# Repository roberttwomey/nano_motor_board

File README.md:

# nano-motor-board
a motor driver adapter for use with 3-axis GRBL.
connects arduino nano to pololu driver boards.

rtwomey@ysu.edu
2017

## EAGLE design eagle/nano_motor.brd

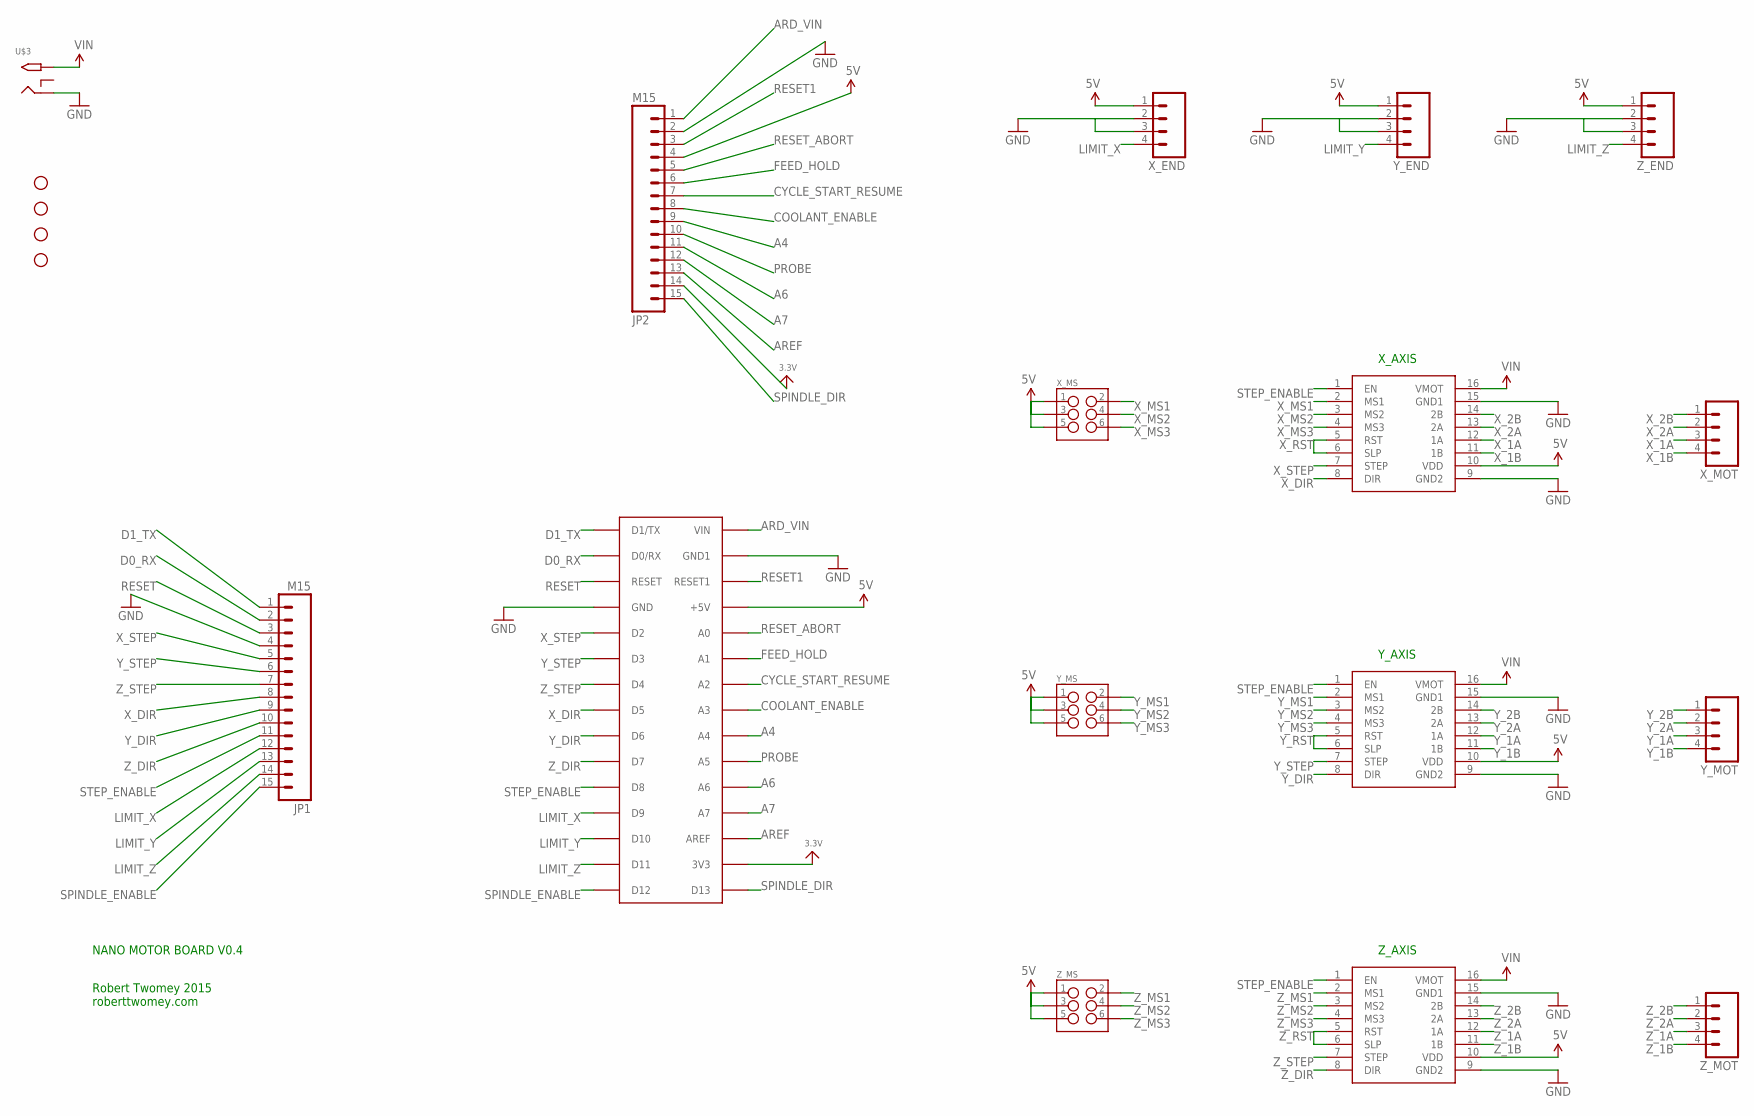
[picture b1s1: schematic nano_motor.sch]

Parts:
JP1, JP2: M15; 1X15
NANO: ARDUINONANO; PDIP-32
STANDOFF1, STANDOFF2, STANDOFF3, STANDOFF4: STAND-OFF
U$3: 2.1MMJACKTHM; PJ-102A
X_AXIS: POLOLUESTEPPERDRIVER; DIL16
X_END: M04PTH; 1X04
X_MOT: M04PTH; 1X04
X_MS: M03X22X3_SILK_SM; 2X3
Y_AXIS: POLOLUESTEPPERDRIVER; DIL16
Y_END: M04PTH; 1X04
Y_MOT: M04PTH; 1X04
Y_MS: M03X22X3_SILK_SM; 2X3
Z_AXIS: POLOLUESTEPPERDRIVER; DIL16
Z_END: M04PTH; 1X04
Z_MOT: M04PTH; 1X04
Z_MS: M03X22X3_SILK_SM; 2X3

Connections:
3.3V: JP2.14, NANO.3V3
5V: JP2.4, NANO.+5V, X_AXIS.10 (VDD), X_END.1, X_MS.1, X_MS.3, X_MS.5, Y_AXIS.10 (VDD), Y_END.1, Y_MS.1, Y_MS.3, Y_MS.5, Z_AXIS.10 (VDD), Z_END.1, Z_MS.1, Z_MS.3, Z_MS.5
A4: JP2.9, NANO.A4
A6: JP2.11, NANO.A6
A7: JP2.12, NANO.A7
ARD_VIN: JP2.1, NANO.VIN
AREF: JP2.13, NANO.AREF
COOLANT_ENABLE: JP2.8, NANO.A3
CYCLE_START_RESUME: JP2.7, NANO.A2
D0_RX: JP1.2, NANO.D0/RX
D1_TX: JP1.1, NANO.D1/TX
FEED_HOLD: JP2.6, NANO.A1
GND: JP1.4, JP2.2, NANO.GND, NANO.GND1, U$3.RING, X_AXIS.9 (GND2), X_AXIS.15 (GND1), X_END.2, X_END.3, Y_AXIS.9 (GND2), Y_AXIS.15 (GND1), Y_END.2, Y_END.3, Z_AXIS.9 (GND2), Z_AXIS.15 (GND1), Z_END.2, Z_END.3
LIMIT_X: JP1.12, NANO.D9, X_END.4
LIMIT_Y: JP1.13, NANO.D10, Y_END.4
LIMIT_Z: JP1.14, NANO.D11, Z_END.4
PROBE: JP2.10, NANO.A5
RESET: JP1.3, NANO.RESET
RESET1: JP2.3, NANO.RESET1
RESET_ABORT: JP2.5, NANO.A0
SPINDLE_DIR: JP2.15, NANO.D13
SPINDLE_ENABLE: JP1.15, NANO.D12
STEP_ENABLE: JP1.11, NANO.D8, X_AXIS.1 (EN), Y_AXIS.1 (EN), Z_AXIS.1 (EN)
VIN: U$3.TIP, X_AXIS.16 (VMOT), Y_AXIS.16 (VMOT), Z_AXIS.16 (VMOT)
X_1A: X_AXIS.12 (1A), X_MOT.3
X_1B: X_AXIS.11 (1B), X_MOT.4
X_2A: X_AXIS.13 (2A), X_MOT.2
X_2B: X_AXIS.14 (2B), X_MOT.1
X_DIR: JP1.8, NANO.D5, X_AXIS.8 (DIR)
X_MS1: X_AXIS.2 (MS1), X_MS.2
X_MS2: X_AXIS.3 (MS2), X_MS.4
X_MS3: X_AXIS.4 (MS3), X_MS.6
X_RST: X_AXIS.5 (RST), X_AXIS.6 (SLP)
X_STEP: JP1.5, NANO.D2, X_AXIS.7 (STEP)
Y_1A: Y_AXIS.12 (1A), Y_MOT.3
Y_1B: Y_AXIS.11 (1B), Y_MOT.4
Y_2A: Y_AXIS.13 (2A), Y_MOT.2
Y_2B: Y_AXIS.14 (2B), Y_MOT.1
Y_DIR: JP1.9, NANO.D6, Y_AXIS.8 (DIR)
Y_MS1: Y_AXIS.2 (MS1), Y_MS.2
Y_MS2: Y_AXIS.3 (MS2), Y_MS.4
Y_MS3: Y_AXIS.4 (MS3), Y_MS.6
Y_RST: Y_AXIS.5 (RST), Y_AXIS.6 (SLP)
Y_STEP: JP1.6, NANO.D3, Y_AXIS.7 (STEP)
Z_1A: Z_AXIS.12 (1A), Z_MOT.3
Z_1B: Z_AXIS.11 (1B), Z_MOT.4
Z_2A: Z_AXIS.13 (2A), Z_MOT.2
Z_2B: Z_AXIS.14 (2B), Z_MOT.1
Z_DIR: JP1.10, NANO.D7, Z_AXIS.8 (DIR)
Z_MS1: Z_AXIS.2 (MS1), Z_MS.2
Z_MS2: Z_AXIS.3 (MS2), Z_MS.4
Z_MS3: Z_AXIS.4 (MS3), Z_MS.6
Z_RST: Z_AXIS.5 (RST), Z_AXIS.6 (SLP)
Z_STEP: JP1.7, NANO.D4, Z_AXIS.7 (STEP)

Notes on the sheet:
X_AXIS
Y_AXIS
Z_AXIS
NANO MOTOR BOARD V0.4
Robert Twomey 2015 roberttwomey.com

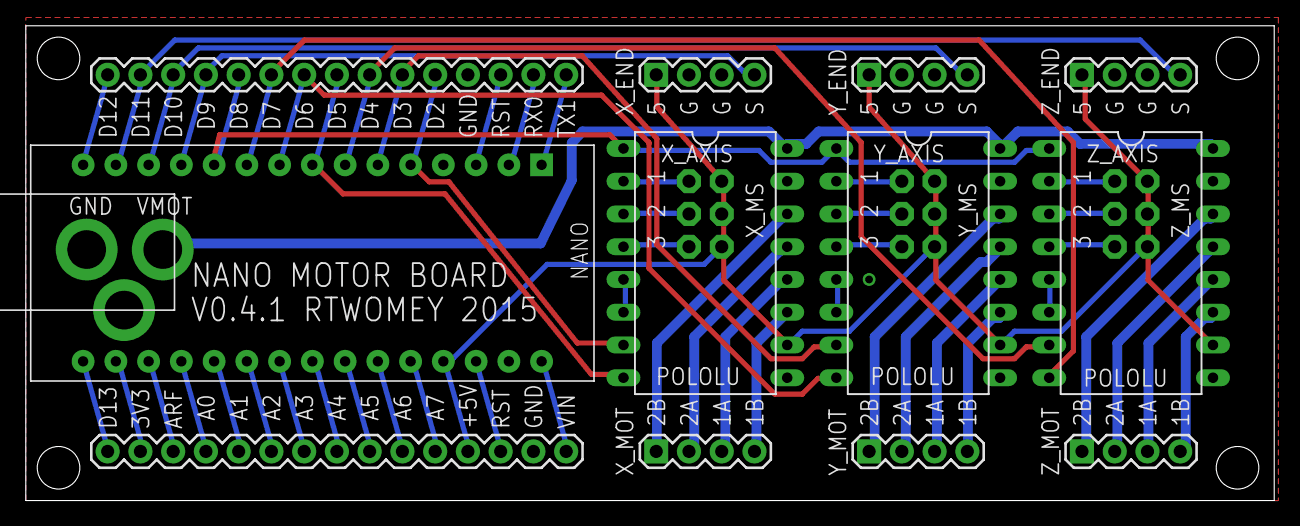
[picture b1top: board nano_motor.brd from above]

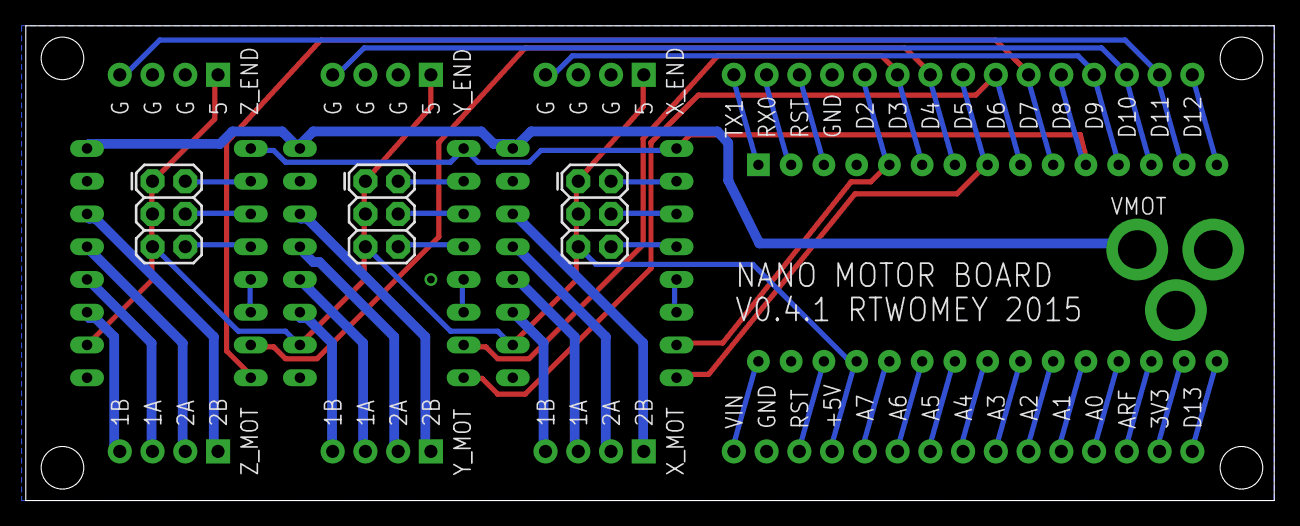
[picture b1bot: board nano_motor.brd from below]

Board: 2 copper layers, 96.8 x 36.8 mm, 20 parts (3 on the bottom side), 54 nets.

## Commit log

2017-01-20 moved photos, added read

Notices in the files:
parts and their libraries:
SparkFun-Connectors: Licensing: Creative Commons ShareAlike 4.0 International - https://creativecommons.org/licenses/by-sa/4.0
microbuilder: This work is placed in the public domain, and may be freely used for commercial and non-commercial work with the following conditions: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
